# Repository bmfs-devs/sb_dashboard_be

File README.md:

# sb_dashboard_be

## Setup

### Backend
- Clone The Repository
- Run command `go mod tidy`
- Install Redis server (if use Windows then you must install Docker or WSL)
- Ask the admin regarding credential of HiveMQ
    ```
    // mqttPass := os.Getenv("MQTT_PASS")
	// mqttuser := os.Getenv("MQTT_USER")
	// mqttAddr := os.Getenv("MQTT_ADDR")
    ```
- Run command `go run app/http/http.go`

### Hardware
#### AC Transmitter and Sensor
- Connect ESP32 to PC/Laptop
- Flash the firmware to ESP32 (`mqtt.ino`)
- Automatic compiled with the other files (`acTransmitter.ino` and `dhtSensor.ino`)
#### AC Infrared Receiver
- Connect ESP32 to PC/Laptop
- Flash the firmware to ESP32 (`receiver.ino`)
- Writedown the Hex output to be used later in the constant.go

### Documentation
- Import `sb_dashboard.postman_collection.json` to Postman
- Test the API endpoints
- If you update the API endpoints, please update the Postman collection as well

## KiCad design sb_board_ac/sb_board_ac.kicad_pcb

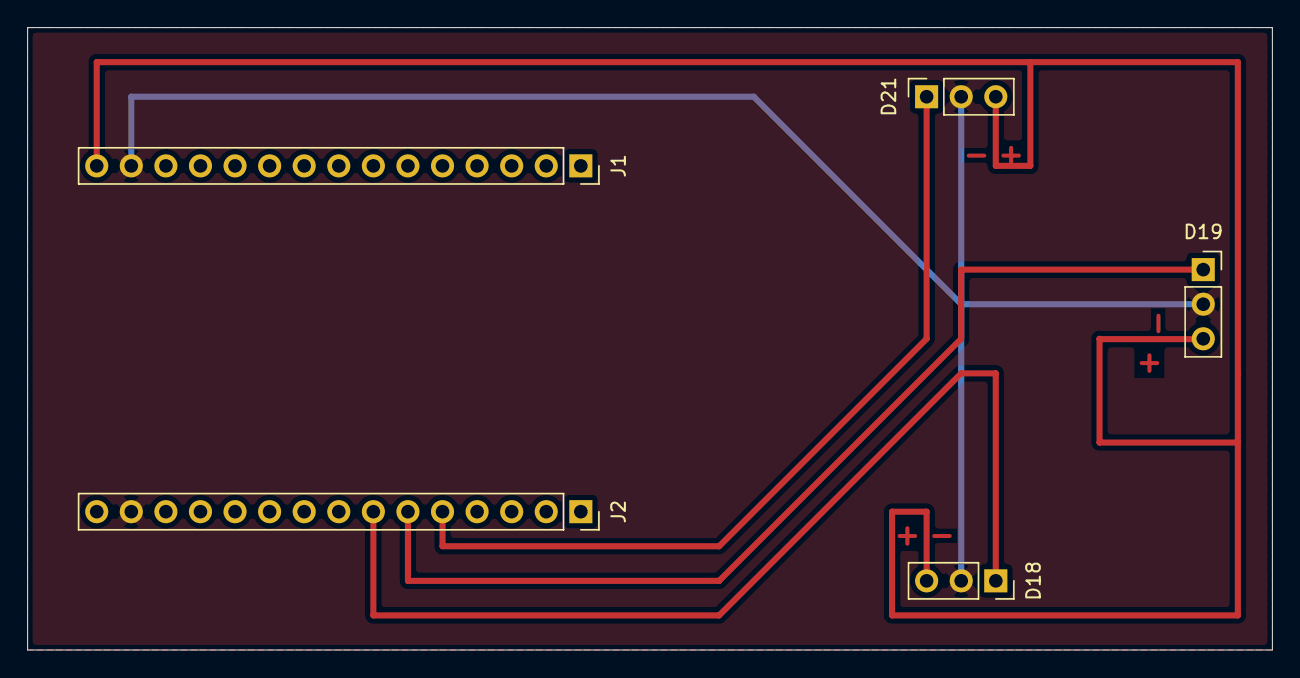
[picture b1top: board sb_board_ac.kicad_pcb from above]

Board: 2 copper layers, 91.4 x 45.7 mm, 5 parts (0 on the bottom side), 5 nets.

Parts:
D18, D19, D21: Conn_01x03_Pin; PinSocket_1x03_P2.54mm_Vertical
J1, J2: Conn_01x15_Pin; PinSocket_1x15_P2.54mm_Vertical

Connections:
/d18: D18.1, J2.7
/d19: D19.1, J2.6
/d21: D21.1, J2.5
/gnd: D18.2, D19.2, D21.2, J1.14, J2.14
/vin: D18.3, D19.3, D21.3, J1.15

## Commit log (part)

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2026-05-18 Add Redis integration for AC temperature management and enhance error handling
    - Introduced Redis repository methods for setting, getting, and deleting AC temperatures.
    - Added temperature handling in use cases and updated the OnOffHandler to manage temperature settings.
    - Created new models for temperature requests and responses.
    - Enhanced error responses in handlers to provide structured JSON output.
    - Updated routes to include a new endpoint for setting AC temperature.
2026-05-19 Add GetTemperature functionality and update routes for temperature handling
2026-05-19 Add MQTT client implementation for AC control and setup WiFi connection
2026-05-20 Add Postman collection for AC remote control and temperature management
2026-05-23 Update log message to include port number for HiveMQ Cloud connection
2026-05-25 fix(ac remote): update hex, add delay and fix switch
    prepend "24" to each entry in Temperature24 constant map
    switch OnOffAC handler to use acStatus.Status instead of ACNumber
    add 500ms sleep before publishing to prevent MQTT message flooding
    add missing time import for sleep functionality
2026-05-25 perf(remote): cut sleep time from 500ms to 50ms
    shorten total execution time of AC remote control sequences by trimming excessive delay between signal steps, while preserving command reliability
2026-05-25 docs(readme): add setup, hardware and postman docs
    add detailed backend setup steps, ESP32 hardware guide and Postman collection usage details to help new contributors get started quickly
2026-05-30 cmmitng
2026-06-08 Add lock files for PCB, project, and schematic in sb_board_ac
    - Created lock files for the PCB, project, and schematic to manage concurrent access.
    - Lock files include hostname and username for tracking purposes.
